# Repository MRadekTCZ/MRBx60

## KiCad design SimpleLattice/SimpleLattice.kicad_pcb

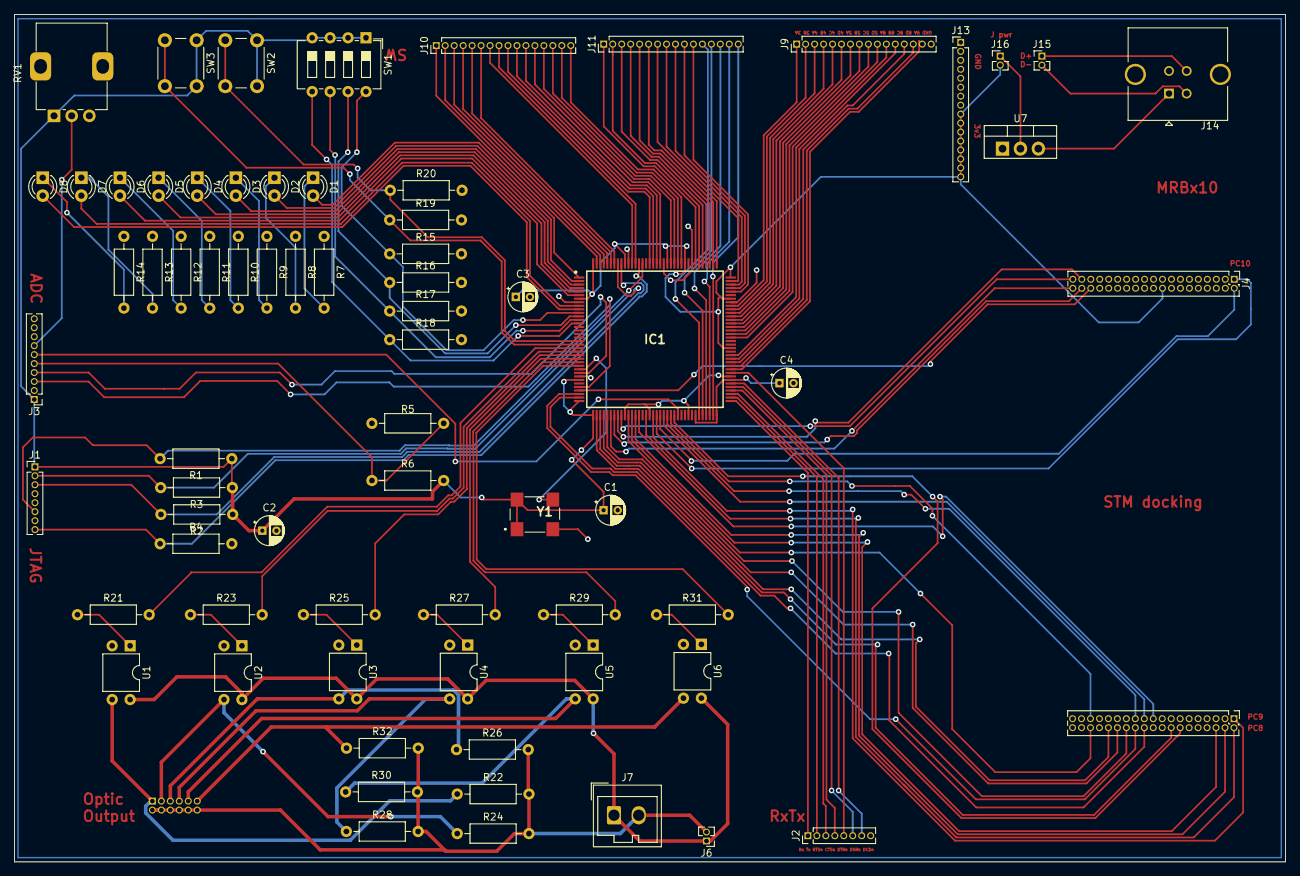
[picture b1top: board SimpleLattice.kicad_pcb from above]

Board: 2 copper layers, 180.0 x 120.0 mm, 72 parts (1 on the bottom side), 135 nets.

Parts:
C1, C2, C3, C4: 0.1uF; CP_Radial_D4.0mm_P2.00mm
D1, D2, D3, D4, D5, D6, D7, D8: LED; LED_D3.0mm
IC1: LCMXO2-1200ZE-1TG144C; QFP50P2200X2200X160-144N
J1, J2: Conn_01x08_Pin; PinHeader_1x08_P1.27mm_Vertical
J3: Conn_01x10_Pin; PinHeader_1x10_P1.27mm_Vertical
J4, J5: Conn_02x19_Odd_Even; PinHeader_2x19_P1.27mm_Vertical
J6: Conn_01x02; PinHeader_1x02_P1.27mm_Vertical
J7: Conn_01x02; Wago_734-132_1x02_P3.50mm_Vertical
J8: Conn_02x06_Odd_Even; PinHeader_2x06_P1.27mm_Vertical
J9, J10, J11, J13: Conn_01x16_Pin; PinHeader_1x16_P1.27mm_Vertical
J14: USB_B; USB_B_Amphenol_MUSB-D511_Vertical_Rugged
J15, J16: Conn_01x02_Pin; PinHeader_1x02_P1.27mm_Vertical
R1, R2, R3, R4, R15, R16, R17, R18, R19, R20, R22, R24, R26, R28, R30, R32: 4k7; R_Axial_DIN0207_L6.3mm_D2.5mm_P10.16mm_Horizontal
R5, R6: 0ohm; R_Axial_DIN0207_L6.3mm_D2.5mm_P10.16mm_Horizontal
R7, R8, R9, R10, R11, R12, R13, R14: 220R; R_Axial_DIN0207_L6.3mm_D2.5mm_P10.16mm_Horizontal
R21, R23, R25, R27, R29, R31: 330R; R_Axial_DIN0207_L6.3mm_D2.5mm_P10.16mm_Horizontal
RV1: R_Potentiometer; Potentiometer_Alps_RK09K_Single_Vertical
SW1: SW_DIP_x04; SW_DIP_SPSTx04_Slide_6.7x11.72mm_W7.62mm_P2.54mm_LowProfile
SW2, SW3: SW_Push; SW_PUSH_6mm_H4.3mm
U1, U2, U3, U4, U5, U6: PC817; DIP-4_W7.62mm
U7: LD1117S50TR_SOT223; TO-220-3_Vertical
Y1: CB3LV-3C-50M0000; CB3LV3C50M0000

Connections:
3V3: C1.1, C2.1, C3.1, C4.1, IC1.7 (VCCIO3_1), IC1.16 (VCCIO3_2), IC1.30 (VCCIO3_3), IC1.36 (VCC_1), IC1.37 (VCCIO2_1), IC1.51 (VCCIO2_2), IC1.66 (VCCIO2_3), IC1.72 (VCC_2), IC1.79 (VCCIO1_1), IC1.88 (VCCIO1_2), IC1.102 (VCCIO1_3), IC1.108 (VCC_3), IC1.118 (VCCIO0_1), IC1.123 (VCCIO0_2), IC1.135 (VCCIO0_3), IC1.144 (VCC_4), J1.1, J3.1, J4.18, J13.9, J13.10, J13.11, J13.12, J13.13, J13.14, J13.15, J13.16, J16.2, R1.1, R2.1, R3.1, R6.2, RV1.1, SW1.1, SW1.2, SW1.3, SW1.4, SW2.1, SW3.1, Y1.1 (EOH), Y1.4 (VCC)
A0: J3.7, RV1.2
ADC_ALERT: IC1.61 (PB18A), J3.6
ADC_SCL: IC1.32 (PL10A), J3.3
ADC_SDA: IC1.28 (PL9B), J3.4
CLK: IC1.27 (PL9A), Y1.3 (OUTPUT)
CTSn: IC1.76 (PR10A), J2.4
DCDn: IC1.78 (PR9C), J2.7
DSRn: IC1.77 (PR9D), J2.6
DTRn: IC1.81 (PR9B), J2.5
Ext_GND: J6.2, J7.2, J8.2, J8.4, J8.6, J8.8, J8.10, J8.12, R22.2, R24.2, R26.2, R28.2, R30.2, R32.2
Ext_VCC: J6.1, J7.1, U1.4, U2.4, U3.4, U4.4, U5.4, U6.4
GND: C1.2, C2.2, C3.2, C4.2, IC1.8 (GND_1), IC1.18 (GND_2), IC1.29 (GND_3), IC1.46 (GND_4), IC1.53 (GND_5), IC1.64 (GND_6), IC1.80 (GND_7), IC1.90 (GND_8), IC1.101 (GND_9), IC1.116 (GND_10), IC1.124 (GND_11), IC1.134 (GND_12), J1.7, J3.2, J4.20, J4.22, J9.16, J13.1, J13.2, J13.3, J13.4, J13.5, J13.6, J13.7, J13.8, J14.4 (GND), R4.2, R5.1, R7.1, R8.1, R9.1, R10.1, R11.1, R12.1, R13.1, R14.1, R15.2, R16.2, R17.2, R18.2, R19.2, R20.2, RV1.3, U1.2, U2.2, U3.2, U4.2, U5.2, U6.2, U7.1 (GND), Y1.2 (GND)
J11_8: IC1.107 (PR2A), J11.8
J11_9: IC1.106 (PR2B), J11.9
J11_10: IC1.105 (PR2C), J11.10
J11_11: IC1.104 (PR2D), J11.11
J11_12: IC1.67 (PB18D), J11.12
J11_13: IC1.68 (PB20A), J11.13
J11_14: IC1.69 (PB20B), J11.14
J11_15: IC1.70 (PB20C), J11.15
J11_16: IC1.71 (PB20D), J11.16
KEY0: IC1.19 (PL5A), R20.1, SW2.2
KEY1: IC1.20 (PL5B), R19.1, SW3.2
LED0: D1.2 (A), IC1.1 (PL2A)
LED1: D2.2 (A), IC1.2 (PL2B)
LED2: D3.2 (A), IC1.3 (PL2C)
LED3: D4.2 (A), IC1.4 (PL2D)
LED4: D5.2 (A), IC1.5 (PL3A)
LED5: D6.2 (A), IC1.6 (PL3B)
LED6: D7.2 (A), IC1.9 (PL3C)
LED7: D8.2 (A), IC1.10 (PL3D)
unnamed: D1.1 (K), R7.2
unnamed: D2.1 (K), R8.2
unnamed: D3.1 (K), R9.2
unnamed: D4.1 (K), R10.2
unnamed: D5.1 (K), R11.2
unnamed: D6.1 (K), R12.2
unnamed: D7.1 (K), R13.2
unnamed: D8.1 (K), R14.2
unnamed: IC1.100 (PR3A), J9.1
unnamed: IC1.99 (PR3B), J9.2
unnamed: IC1.98 (PR4A), J9.3
unnamed: IC1.97 (PR4B), J9.4
unnamed: IC1.96 (PR4C), J9.5
unnamed: IC1.95 (PR4D), J9.6
unnamed: IC1.94 (PR5A), J9.7
unnamed: IC1.93 (PR5B), J9.8
unnamed: IC1.92 (PR5C), J9.9
unnamed: IC1.91 (PR5D), J9.10
unnamed: IC1.86 (PR8A), J9.11
unnamed: IC1.85 (PR8B), J9.12
unnamed: IC1.84 (PR8C), J9.13
unnamed: IC1.83 (PR8D), J9.14
unnamed: IC1.82 (PR9A), J9.15
unnamed: IC1.143 (PT9A), J10.1
unnamed: IC1.142 (PT9B), J10.2
unnamed: IC1.141 (PT9C), J10.3
unnamed: IC1.140 (PT9D), J10.4
unnamed: IC1.139 (PT10A), J10.5
unnamed: IC1.138 (PT10B), J10.6
unnamed: IC1.133 (PT11A), J10.7
unnamed: IC1.132 (PT11B), J10.8
unnamed: IC1.128 (PT12A), J10.9
unnamed: IC1.127 (PT12B), J10.10
unnamed: IC1.126 (PT12C), J10.11
unnamed: IC1.125 (PT12D), J10.12
unnamed: IC1.122 (PT15A), J10.13
unnamed: IC1.121 (PT15B), J10.14
unnamed: IC1.120 (PT15C), J10.15
unnamed: IC1.119 (PT15D), J10.16
unnamed: IC1.115 (PT16B), J11.1
unnamed: IC1.114 (PT16C), J11.2
unnamed: IC1.113 (PT16D), J11.3
unnamed: IC1.112 (PT17A), J11.4
unnamed: IC1.111 (PT17B), J11.5
unnamed: IC1.110 (PT17C), J11.6
unnamed: IC1.109 (PT17D), J11.7
unnamed: J3.5, R5.2, R6.1
unnamed: J14.3 (D+), J15.1
unnamed: J14.2 (D-), J15.2
unnamed: J16.1, U7.2 (VO)
unnamed: R21.1, U1.1
unnamed: R23.1, U2.1
unnamed: R25.1, U3.1
unnamed: R27.1, U4.1
unnamed: R29.1, U5.1
unnamed: R31.1, U6.1
OPTO1: IC1.21 (PL5C), R21.2
OPTO2: IC1.22 (PL5D), R23.2
OPTO3: IC1.23 (PL8A), R25.2
OPTO4: IC1.24 (PL8B), R27.2
OPTO5: IC1.25 (PL8C), R29.2
OPTO6: IC1.26 (PL8D), R31.2
OUT1: J8.1, R22.1, U1.3
OUT2: J8.3, R24.1, U2.3
OUT3: J8.5, R26.1, U3.3
OUT4: J8.7, R28.1, U4.3
OUT5: J8.9, R30.1, U5.3
OUT6: J8.11, R32.1, U6.3
PA8: IC1.58 (PB15B), J5.23
PA9: IC1.57 (PB15A), J5.21
PA10: IC1.59 (PB15C), J5.33
PA11: IC1.60 (PB15D), J5.14
PB0: IC1.33 (PL10B), J4.34
PB1: IC1.34 (PL10C), J5.24
PB2: IC1.35 (PL10D), J5.22
PB12: IC1.38 (PB4A), J5.16
PB13: IC1.39 (PB4B), J5.30
PB14: IC1.40 (PB4C), J5.28
PB15: IC1.41 (PB4D), J5.26
PC0: IC1.42 (PB6A), J4.38
PC1: IC1.43 (PB6B), J4.36
PC2: IC1.44 (PB6C), J4.35
PC3: IC1.45 (PB6D), J4.37
PC4: IC1.47 (PB9C), J5.34
PC5: IC1.48 (PB9D), J5.6
PC6: IC1.49 (PB9A), J5.4
PC7: IC1.50 (PB9B), J5.19
PC8: IC1.52 (PB11C), J5.2
PC9: IC1.54 (PB11D), J5.1
PC10: IC1.55 (PB11A), J4.1
PC11: IC1.56 (PB11B), J4.2
RTSn: IC1.75 (PR10B), J2.3
Rx: IC1.73 (PR10D), J2.1
SW0: IC1.11 (PL4A), R15.1, SW1.8
SW1: IC1.12 (PL4B), R16.1, SW1.7
SW2: IC1.13 (PL4C), R17.1, SW1.6
SW3: IC1.14 (PL4D), R18.1, SW1.5
TCK: IC1.131 (PT11C), J1.8, R4.1
TDI: IC1.136 (PT10D), J1.3, R2.2
TDO: IC1.137 (PT10C), J1.2, R3.2
TMS: IC1.130 (PT11D), J1.6, R1.2
Tx: IC1.74 (PR10C), J2.2
VCC5V: J14.1 (VBUS), U7.3 (VI)

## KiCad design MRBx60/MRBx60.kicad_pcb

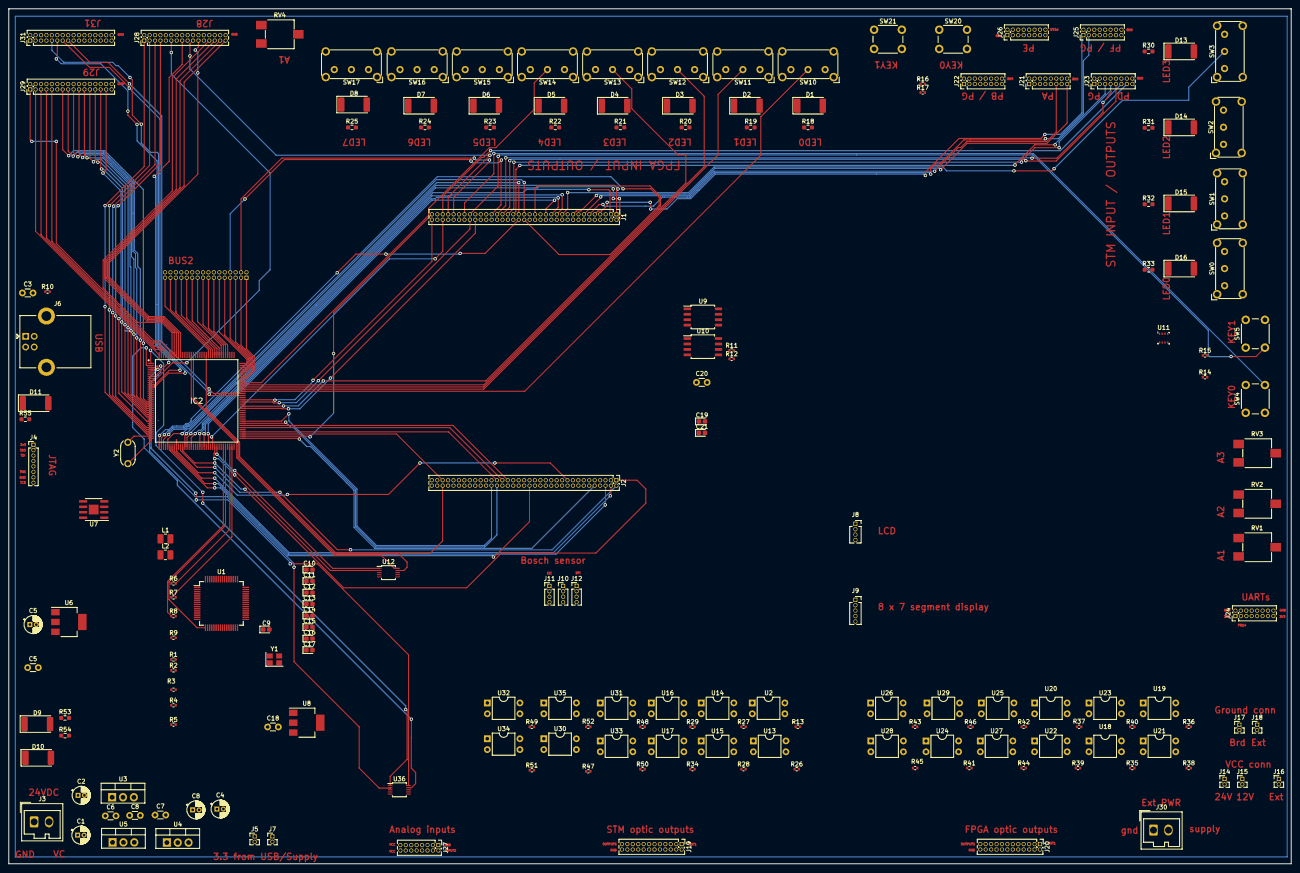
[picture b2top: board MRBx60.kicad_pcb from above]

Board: 2 copper layers, 300.0 x 200.0 mm, 185 parts (1 on the bottom side), 246 nets.

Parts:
C1: 0.1uF; CP_Radial_D4.0mm_P1.50mm
C2, C4, C8#2: 1uF; CP_Radial_D4.0mm_P1.50mm
C3, C6, C7: 0.1uF; C_Disc_D3.0mm_W1.6mm_P2.50mm
C5, C18: 1uF; C_Disc_D3.0mm_W1.6mm_P2.50mm
C5#2: C_Polarized; CP_Radial_D4.0mm_P1.50mm
C8: C; C_Disc_D3.0mm_W1.6mm_P2.50mm
C9, C11, C13, C15: 0.1uF; CP_EIA-1608-08_AVX-J
C10, C12: 4uF; CP_EIA-1608-08_AVX-J
C14: 10uF; CP_EIA-1608-08_AVX-J
C16, C17: 18pF; CP_EIA-1608-08_AVX-J
C19, C21: 100nF; CP_EIA-1608-08_AVX-J
C20: 10uF; C_Disc_D3.0mm_W1.6mm_P2.50mm
D1, D2, D3, D4, D5, D6, D7, D8, D9, D10, D11, D13, D14, D15, D16: LED; LED_2512_6332Metric_Pad1.52x3.35mm_HandSolder
IC2: ICE40HX1K-TQ144; QFP50P2200X2200X160-144N
J1, J2: Conn_02x35_Odd_Even; PinHeader_2x35_P1.27mm_Vertical
J3, J30: Conn_01x02; Wago_734-132_1x02_P3.50mm_Vertical
J4: Conn_01x08_Pin; PinHeader_1x08_P1.27mm_Vertical
J5, J7, J14, J15, J16, J17, J18: Conn_01x02_Pin; PinHeader_1x02_P1.27mm_Vertical
J6: USB_B; USB_B_Lumberg_2411_02_Horizontal
J8: Conn_01x04_Socket; PinSocket_1x04_P1.27mm_Vertical
J9: Conn_01x05_Socket; PinSocket_1x05_P1.27mm_Vertical
J10, J11, J12: Conn_01x04_Pin; PinHeader_1x04_P1.27mm_Vertical
J13, J28, J29, J31: Conn_02x16_Odd_Even; PinHeader_2x16_P1.27mm_Vertical
J19, J20: Conn_02x12_Odd_Even; PinHeader_2x12_P1.27mm_Vertical
J21, J22, J23, J24, J25, J26, J27: Conn_02x08_Odd_Even; PinHeader_2x08_P1.27mm_Vertical
L1, L2: 0.1uH; L_1008_2520Metric_Pad1.43x2.20mm_HandSolder
R1, R3, R4, R5: 1k; R_0402_1005Metric
R2: 10k; R_0402_1005Metric
R6, R7, R8, R9, R10: 5k; R_0402_1005Metric
R11, R12, R13, R14, R15, R16, R17, R26, R27, R28, R29, R34, R35, R36, R37, R38, R39, R40, R41, R42, R43, R44, R45, R46, R47, R48, R49, R50, R51, R52: 4k7; R_0402_1005Metric
R18, R19, R20, R21, R22, R23, R24, R25, R30, R31, R32, R33, R53, R54, R55: 220R; R_0603_1608Metric_Pad0.98x0.95mm_HandSolder
RV1, RV2, RV3, RV4: R_Potentiometer; Potentiometer_ACP_CA6-VSMD_Vertical
SW0, SW1, SW2, SW3, SW10, SW11, SW12, SW13, SW14, SW15, SW16, SW17: SW_Reed_SPDT; SW_E-Switch_EG1224_SPDT_Angled
SW4, SW5, SW20, SW21: SW_Push_Dual_x2; SW_PUSH_6mm
U1: FT2232HL; LQFP-64_10x10mm_P0.5mm
U2, U13, U14, U15, U16, U17, U18, U19, U20, U21, U22, U23, U24, U25, U26, U27, U28, U29, U30, U31, U32, U33, U34, U35: PC817; DIP-4_W7.62mm
U3: L7812; TO-220-3_Vertical
U4: L7805; TO-220-3_Vertical
U5: L7824; TO-220-3_Vertical
U6, U8: TC1262-33; SOT-223
U7: 93LCxxC; HSOP-8-1EP_3.9x4.9mm_P1.27mm_EP2.3x2.3mm
U9: 24LC02; SOIC-8W_5.3x5.3mm_P1.27mm
U10: 93AAxxA; SOIC-8W_5.3x5.3mm_P1.27mm
U11: BME280; Bosch_LGA-8_2.5x2.5mm_P0.65mm_ClockwisePinNumbering
U12, U36: ADS1115IDGS; TSSOP-10_3x3mm_P0.5mm
Y1: 12MHz; Crystal_SMD_SeikoEpson_FA238-4Pin_3.2x2.5mm
Y2: 50MHz; Resonator-2Pin_W6.0mm_H3.0mm

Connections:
/Programmer/EECS: U1.63 (EECS), U7.1 (CS)
AGND: J2.32, RV1.3, RV2.3, RV3.3
DC3_3: C5.1, C5#2.1, C9.1, D9.2 (A), IC2.6 (VCCIO_3_1), IC2.30 (VCCIO_3_2), IC2.46 (VCCIO_2_1), IC2.57 (VCCIO_2_2), IC2.72 (VCC_SPI), IC2.89 (VCCIO_1_1), IC2.100 (VCCIO_1_2), IC2.123 (VCCIO_0_1), IC2.133 (VCCIO_0_2), J4.1, J27.15, J27.16, J28.2, J28.4, J28.6, J28.8, J28.10, J28.12, J28.14, J28.16, J29.2, J29.4, J29.6, J29.8, J29.10, J29.12, J29.14, J29.16, J31.2, J31.4, J31.6, J31.8, J31.10, J31.12, J31.14, J31.16, L1.1, L2.1, R3.2, R7.2, R8.2, R9.2, R16.1, R17.1, RV4.1, SW10.1, SW11.1, SW12.1, SW13.1, SW14.1, SW15.1, SW16.1, SW17.1, U1.20 (VCCIO), U1.31 (VCCIO), U1.42 (VCCIO), U1.50 (VREGIN), U1.56 (VCCIO), U6.3 (VO), U7.6 (ORG), U7.8 (VCC), U12.8 (VDD), U36.8 (VDD)
DC3_3_STM: C18.1, C20.1, C21.1, D10.2 (A), U8.3 (VO), U11.6 (VDDIO), U11.8 (VDD)
DC5: C4.1, C8.1, C19.1, J5.1, J8.3, J9.1, R11.1, R12.1, U4.3 (OUT), U8.1 (VI), U9.8 (VCC), U10.8 (VCC)
DC12: C7.1, C8#2.1, J15.2, U3.3 (OUT), U4.1 (IN)
DC24: C2.1, C6.1, J14.2, U3.1 (IN), U5.3 (OUT)
DM: J6.2 (D-), U1.7 (DM)
DP: J6.3 (D+), U1.8 (DP)
Ext_GND: J17.1, J18.1, J19.2, J19.4, J19.6, J19.8, J19.10, J19.12, J19.14, J19.16, J19.18, J19.20, J19.22, J19.24, J20.2, J20.4, J20.6, J20.8, J20.10, J20.12, J20.14, J20.16, J20.18, J20.20, J20.22, J20.24, R13.2, R26.2, R27.2, R28.2, R29.2, R34.2, R35.2, R36.2, R37.2, R38.2, R39.2, R40.2, R41.2, R42.2, R43.2, R44.2, R45.2, R46.2, R47.2, R48.2, R49.2, R50.2, R51.2, R52.2
Ext_PWR: J14.1, J15.1, J16.1, U2.4, U13.4, U14.4, U15.4, U16.4, U17.4, U18.4, U19.4, U20.4, U21.4, U22.4, U23.4, U24.4, U25.4, U26.4, U27.4, U28.4, U29.4, U30.4, U31.4, U32.4, U33.4, U34.4, U35.4
GND: C1.2, C2.2, C3.2, C4.2, C5.2, C5#2.2, C6.2, C7.2, C8.2, C8#2.2, C9.2, C10.2, C11.2, C12.2, C13.2, C16.2, C17.2, C18.2, C19.2, C20.2, C21.2, IC2.5 (GND_1), IC2.13 (GND_2), IC2.14 (GND_3), IC2.59 (GND_4), IC2.69 (GND_5), IC2.86 (GND_6), IC2.103 (GND_7), IC2.132 (GND_8), IC2.140 (GND_9), J1.8, J1.19, J1.20, J1.22, J1.49, J1.60, J2.9, J2.20, J2.39, J2.54, J2.63, J3.1, J4.7, J6.4 (GND), J8.4, J9.2, J17.2, J21.10, J21.12, J21.14, J21.16, J22.10, J22.12, J22.14, J22.16, J23.10, J23.12, J23.14, J23.16, J24.2, J24.10, J24.16, J25.10, J25.12, J25.14, J25.16, J27.1, J27.3, J27.5, J27.7, J27.9, J27.11, J27.13, J28.18, J28.20, J28.22, J28.24, J28.26, J28.28, J28.30, J28.32, J29.18, J29.20, J29.22, J29.24, J29.26, J29.28, J29.30, J29.32, J31.18, J31.20, J31.22, J31.24, J31.26, J31.28, J31.30, J31.32, R6.1, R10.1, R18.2, R19.2, R20.2, R21.2, R22.2, R23.2, R24.2, R25.2, R30.2, R31.2, R32.2, R33.2, R53.2, R54.2, R55.2, RV4.3, SW0.3, SW1.3, SW2.3, SW3.3, SW4.1 (C), SW5.1 (C), SW10.3, SW11.3, SW12.3, SW13.3, SW14.3, SW15.3, SW16.3, SW17.3, SW20.1 (C), SW21.1 (C), U1.1 (GND), U1.5 (GND), U1.10 (AGND), U1.11 (GND), U1.13 (TEST), U1.15 (GND), U1.25 (GND), U1.35 (GND), U1.47 (GND), U1.51 (GND), U2.2, U3.2 (GND), U4.2 (GND), U5.2 (GND), U6.2 (GND), U7.5 (GND), U8.2 (GND), U9.4 (GND), U9.7 (WP), U10.5 (GND), U11.1 (GND), U11.7 (GND), U12.3 (GND), U13.2, U14.2, U15.2, U16.2, U17.2, U18.2, U19.2, U20.2, U21.2, U22.2, U23.2, U24.2, U25.2, U26.2, U27.2, U28.2, U29.2, U30.2, U31.2, U32.2, U33.2, U34.2, U35.2, U36.3 (GND), Y1.2, Y1.4
GNDPLL: IC2.35 (GNDPLL), Y2.2
IOB_24: IC2.37 (IOB_24), J1.38
IOB_25: IC2.38 (IOB_25), J1.36
IOB_26: IC2.39 (IOB_26), J1.35
IOB_27: IC2.41 (IOB_27), J1.37
IOB_28: IC2.42 (IOB_28), J2.34
IOB_29: IC2.43 (IOB_29), J2.6
IOB_30: IC2.44 (IOB_30), J2.4
IOB_31: IC2.45 (IOB_31), J2.19
IOB_32: IC2.47 (IOB_32), J2.2
IOB_33: IC2.48 (IOB_33), J2.1
IOB_34: IC2.52 (IOB_34), J1.3
IOB_35: IC2.49 (IOB_35_GBIN5), J1.1
IOB_36: IC2.50 (IOB_36_GBIN4), J1.2
IOB_37: IC2.56 (IOB_37), J1.23
IOB_38: IC2.58 (IOB_38), J1.25
IOB_39: IC2.60 (IOB_39), J1.27
IOB_40: IC2.61 (IOB_40), J1.63, J22.15, J28.19
IOB_41: IC2.62 (IOB_41), J1.66, J28.17
IOB_42: IC2.63 (IOB_42_CBSEL0), U12.2 (ALERT/RDY)
IOB_43: IC2.64 (IOB_43_CBSEL1), U12.1 (ADDR)
IOB_44: IC2.67 (IOB_44_SDO), J4.2, R8.1, U1.18 (ADBUS2)
IOB_45: IC2.68 (IOB_45_SDI), J4.3, R9.1, U1.17 (ADBUS1)
IOB_46: IC2.70 (IOB_46_SCK), J4.8, R6.2, U1.16 (ADBUS0)
IOB_47: IC2.71 (IOB_47_SS), J4.6, R7.1, U1.19 (ADBUS3)
IOL_1A: IC2.1 (IOL_1A), U36.1 (ADDR)
IOL_1B: IC2.2 (IOL_1B), U36.9 (SDA)
IOL_2A: IC2.3 (IOL_2A), U36.10 (SCL)
IOL_2B: IC2.4 (IOL_2B), U36.2 (ALERT/RDY)
IOL_3A: IC2.7 (IOL_3A), J28.15
IOL_3B: IC2.8 (IOL_3B), J28.13
IOL_4A: IC2.9 (IOL_4A), J28.11
IOL_4B: IC2.10 (IOL_4B), J28.9
IOL_5A: IC2.11 (IOL_5A), J31.11, U19.1
IOL_5B: IC2.12 (IOL_5B), J31.9, U21.1
IOL_6A: D8.2 (A), IC2.19 (IOL_6A), J29.13
IOL_6B: D7.2 (A), IC2.20 (IOL_6B_GBIN7), J29.15
IOL_7A: D6.2 (A), IC2.21 (IOL_7A_GBIN6), J29.17
IOL_7B: IC2.22 (IOL_7B), J29.19, U23.1
IOL_8A: IC2.23 (IOL_8A), J29.21, U18.1
IOL_8B: IC2.24 (IOL_8B), J29.23, U20.1
IOL_9A: IC2.25 (IOL_9A), J29.25, U22.1
IOL_9B: IC2.26 (IOL_9B), J29.27, U25.1
IOL_10A: IC2.28 (IOL_10A), J29.29, U27.1
IOL_10B: IC2.29 (IOL_10B), J29.31, U29.1
IOL_11A: IC2.31 (IOL_11A), J28.7, U24.1
IOL_11B: IC2.32 (IOL_11B), J28.5, U26.1
IOL_12A: IC2.33 (IOL_12A), J28.3, U28.1
IOL_12B: IC2.34 (IOL_12B), J28.1
IOR_48: IC2.73 (IOR_48), J2.10
IOR_49: IC2.74 (IOR_49), J1.69
IOR_50: IC2.75 (IOR_50), J2.65
IOR_51: IC2.76 (IOR_51), J2.45
IOR_52: IC2.78 (IOR_52), J2.43
IOR_53: IC2.79 (IOR_53), J2.41
IOR_54: IC2.80 (IOR_54), J2.46
IOR_55: IC2.81 (IOR_55), J2.48
IOR_56: IC2.87 (IOR_56), J1.54
IOR_57: IC2.88 (IOR_57), J1.31
IOR_58: IC2.90 (IOR_58), J1.56
IOR_59: IC2.91 (IOR_59), J1.70
IOR_60: IC2.93 (IOR_60_GBIN3), J31.13
IOR_61: IC2.94 (IOR_61_GBIN2), J31.15
IOR_62: IC2.95 (IOR_62), SW10.2
IOR_63: IC2.96 (IOR_63), SW11.2
IOR_64: IC2.97 (IOR_64), SW12.2
IOR_65: IC2.98 (IOR_65), SW13.2
IOR_66: IC2.99 (IOR_66), SW14.2
IOR_67: IC2.101 (IOR_67), J1.28, J13.1, J24.13
IOR_68: IC2.102 (IOR_68), J1.30, J13.3, J24.14
IOR_69: IC2.104 (IOR_69), J13.5
IOR_70: IC2.105 (IOR_70), J13.7
IOR_71: IC2.106 (IOR_71), J13.9
IOR_72: IC2.107 (IOR_72), J13.11
IOT_73: IC2.112 (IOT_73), J13.13
IOT_74: IC2.113 (IOT_74), J13.15
IOT_75: IC2.114 (IOT_75), J13.17
IOT_76: IC2.115 (IOT_76), J13.19
IOT_77: IC2.116 (IOT_77), J13.21
IOT_78: IC2.117 (IOT_78), J13.23
IOT_79: IC2.118 (IOT_79), J13.25
IOT_80: IC2.119 (IOT_80), J13.27
IOT_81: IC2.120 (IOT_81), J13.29
IOT_82: IC2.121 (IOT_82), J13.31
IOT_83: IC2.122 (IOT_83), J2.66, J22.13
IOT_84: IC2.128 (IOT_84_GBIN1), U12.9 (SDA)
IOT_85: IC2.129 (IOT_85_GBIN0), U12.10 (SCL)
IOT_87: IC2.134 (IOT_87), J28.21, SW15.2
IOT_88: IC2.135 (IOT_88), J28.31, SW16.2
IOT_89: IC2.136 (IOT_89), J28.29, SW17.2
IOT_90: IC2.137 (IOT_90), J28.27, R16.2, SW20.2 (D)
IOT_91: IC2.138 (IOT_91), J28.25, R17.2, SW21.2 (D)
IOT_92: D1.2 (A), IC2.139 (IOT_92), J29.1
IOT_93: D2.2 (A), IC2.141 (IOT_93), J29.9
IOT_94: D3.2 (A), IC2.142 (IOT_94), J29.7
IOT_95: D4.2 (A), IC2.143 (IOT_95), J29.5
IOT_96: D5.2 (A), IC2.144 (IOT_96), J29.3
NC1: J1.26, J1.67
unnamed: C14.2, C15.2, R2.2
unnamed: D1.1 (K), R18.1
unnamed: D2.1 (K), R19.1
unnamed: D3.1 (K), R20.1
unnamed: D4.1 (K), R21.1
unnamed: D5.1 (K), R22.1
unnamed: D6.1 (K), R23.1
unnamed: D7.1 (K), R24.1
unnamed: D8.1 (K), R25.1
unnamed: D9.1 (K), R53.1
unnamed: D10.1 (K), R54.1
unnamed: D11.2 (A), J6.1 (VBUS), J7.1
unnamed: D11.1 (K), R55.1
unnamed: D13.1 (K), R30.1
unnamed: D14.1 (K), R31.1
unnamed: D15.1 (K), R32.1
unnamed: D16.1 (K), R33.1
unnamed: C1.1, J3.2, U5.1 (IN)
unnamed: J5.2, J7.2, U6.1 (VI)
unnamed: C3.1, J6.5 (Shield), R10.2
unnamed: J10.1, U11.5 (SDO)
unnamed: J10.2, U11.4 (SCK)
unnamed: J10.3, U11.3 (SDI)
unnamed: J10.4, U11.2 (CSB)
unnamed: J16.2, J30.2
unnamed: J18.2, J30.1
unnamed: J27.2, U12.5 (AIN1)
unnamed: J27.4, U12.6 (AIN2)
unnamed: J27.6, U12.7 (AIN3)
unnamed: J27.8, U36.4 (AIN0)
unnamed: J27.10, U36.5 (AIN1)
unnamed: J27.12, U36.6 (AIN2)
unnamed: J27.14, U36.7 (AIN3)
unnamed: R1.2, R5.2
unnamed: R3.1, R4.2
unnamed: U1.62 (EECLK), U7.2 (SCLK)
unnamed: R5.1, U1.61 (EEDATA), U7.3 (DI)
unnamed: R2.1, U1.6 (REF)
unnamed: C10.1, C11.1, L2.2, U1.4 (VPHY)
unnamed: R4.1, U1.14 (~RESET)
unnamed: R1.1, U7.4 (DO)
unnamed: RV4.2, U12.4 (AIN0)
OSCI_FTDI: C16.1, U1.2 (OSCI), Y1.1
OSCO_FTDI: C17.1, U1.3 (OSCO), Y1.3
PA9: J9.5, J12.2, U10.2 (SCLK)
PA_2: J2.35, J24.7
PA_3: J2.37, J24.8
PA_4: J1.32, J21.1, U2.1
PA_5: J2.11, J21.3, RV2.2, U13.1
PA_6: J2.13, J21.5, U14.1
PA_7: J2.15, J2.21, RV1.2
PA_8: J2.23, J21.7
PA_9: J11.3, J24.5
PA_10: J2.33, J24.6
PA_12: J2.12, J21.9, U15.1
PA_13: J1.13, J21.11, U16.1
PA_14: J1.15, J21.13, U17.1
PA_15: J1.17, J21.15
PB14: J12.1, U10.4 (DO)
PB15: J9.3, J12.3, U10.3 (DI)
PB_0: D13.2 (A), J1.34, J22.1
PB_1: D14.2 (A), J2.24, J22.3
PB_2: D15.2 (A), J2.22, J22.5
PB_3: D16.2 (A), J2.31, J22.7
PB_4: J2.27, SW0.2
PB_5: J2.29, SW1.2
PB_6: J2.17, SW2.2
PB_7: J1.21, SW3.2
PB_8: J2.3, J8.1, J11.2, U9.6 (SCL)
PB_9: J2.5, J8.2, R11.2, R12.2, U9.5 (SDA)
PB_14: J2.28, J24.3
PB_15: J2.26, J24.4
PD_0: J1.57, J24.12, R14.2, SW4.2 (D)
PD_1: J1.55, J24.11, R15.2, SW5.2 (D)
PD_2: J1.4, J23.1, U31.1
PD_3: J1.40, J23.3, U33.1
PD_4: J1.39, J23.5, U35.1
PD_5: J1.41, J23.7, U30.1
PD_6: J1.43, J23.9, U32.1
PD_7: J1.45, J23.11, U34.1
PE_0: J2.64, J13.2, J26.1
PE_1: J1.61, J13.4, J26.3
PE_2: J1.46, J13.6, J26.5
PE_3: J1.47, J13.8, J26.7
PE_4: J1.48, J13.10, J26.9
PE_5: J1.50, J13.12, J26.11
PE_6: J1.62, J13.14, J26.13
PE_7: J2.44, J13.16, J26.15
PE_8: J2.40, J13.18, J26.2
PE_9: J2.52, J13.20, J26.4
PE_10: J2.47, J13.22, J26.6
PE_11: J2.56, J13.24, J26.8
PE_12: J2.49, J13.26, J26.10
PE_13: J2.55, J13.28, J26.12
PE_14: J2.51, J13.30, J26.14
PE_15: J2.53, J13.32, J26.16
PF_6: J1.9, J25.1
PF_7: J1.11, J25.3
PF_10: J2.42, J25.5
PF_11: J2.62, J25.7
PF_12: J2.59, J25.9
PF_13: J2.57, J25.11
PF_14: J2.50, RV3.2
PF_15: J2.60, J25.15
PG_6: J2.70, J22.9
PG_7: J2.67, J22.11
PG_12: J1.65, J23.13
PG_13: J1.68, J23.15
PG_14: J2.61, J25.13
V3_3: J1.16, J21.2, J21.4, J21.6, J21.8, J22.2, J22.4, J22.6, J22.8, J23.2, J23.4, J23.6, J23.8, J24.1, J24.9, J24.15, J25.2, J25.4, J25.6, J25.8, R14.1, R15.1, RV1.1, RV2.1, RV3.1, SW0.1, SW1.1, SW2.1, SW3.1
VCC1_8FT: C12.1, C13.1, C14.1, C15.1, L1.2, U1.9 (VPLL), U1.12 (VCORE), U1.37 (VCORE), U1.49 (VREGOUT), U1.64 (VCORE)
VCCPLL: IC2.36 (VCCPLL), Y2.1
opt_fpga1: J20.1, R36.1, U19.3
opt_fpga2: J20.3, R38.1, U21.3
opt_fpga3: J20.5, R40.1, U23.3
opt_fpga4: J20.7, R35.1, U18.3
opt_fpga5: J20.9, R37.1, U20.3
opt_fpga6: J20.11, R39.1, U22.3
opt_fpga7: J20.13, R42.1, U25.3
opt_fpga8: J20.15, R44.1, U27.3
opt_fpga9: J20.17, R46.1, U29.3
opt_fpga10: J20.19, R41.1, U24.3
opt_fpga11: J20.21, R43.1, U26.3
opt_fpga12: J20.23, R45.1, U28.3
opt_stm1: J19.1, R13.1, U2.3
opt_stm2: J19.3, R26.1, U13.3
opt_stm3: J19.5, R27.1, U14.3
opt_stm4: J19.7, R28.1, U15.3
opt_stm5: J19.9, R29.1, U16.3
opt_stm6: J19.11, R34.1, U17.3
opt_stm7: J19.13, R48.1, U31.3
opt_stm8: J19.15, R50.1, U33.3
opt_stm9: J19.17, R52.1, U35.3
opt_stm10: J19.19, R47.1, U30.3
opt_stm11: J19.21, R49.1, U32.3
opt_stm12: J19.23, R51.1, U34.3

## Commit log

2023-04-12 Add files via upload
    duzo zmian dodane fpga i stm wyrpowadzenia
2023-04-15 Add files via upload
    rozwoj, do dodania jeszcze GPIO, optic, i wszystko rozmiescic na plytce
2023-04-15 Add files via upload
    kopia rar
2023-04-16 Add files via upload
    Płytka ukończona, pozostaje połączyć ścieżki
2023-04-17 Add files via upload
    dodawanie ścieżek, podejscie 1
2023-04-18 Add files via upload
    Prosta płytka umozliwiajaca test lattice fpga oraz polaczenie z STM 16 bit dane / 7 bit adresu
2023-04-19 Add files via upload
    kolejne połączenia dodano stabilizator 3v3
2023-04-19 Add files via upload
    caly folder
2023-04-19 Add files via upload
    kolejne polaczenia v2
2023-04-20 Add files via upload
    kolejnme p-olaczenia prawie koniec
